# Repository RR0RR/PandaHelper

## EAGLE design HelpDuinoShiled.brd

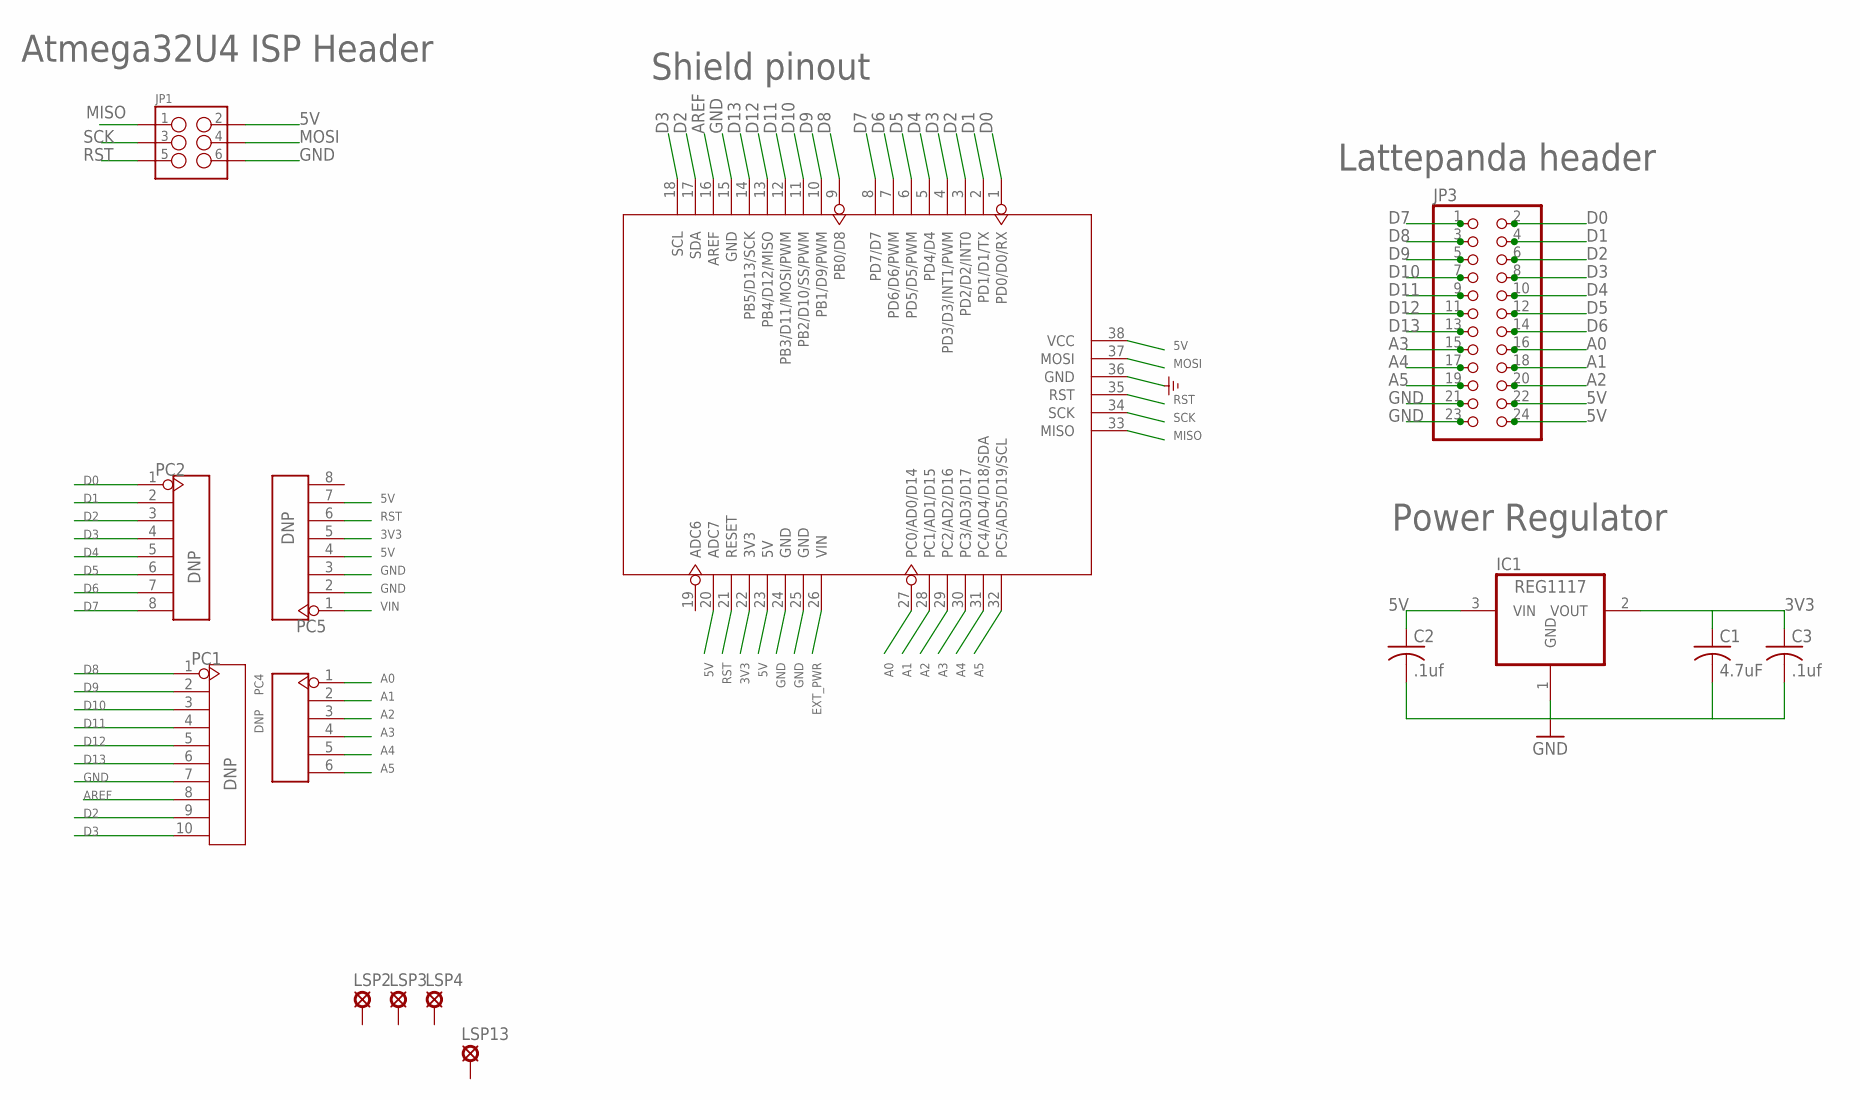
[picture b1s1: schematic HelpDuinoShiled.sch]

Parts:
C1: 4.7uF; C0603K
C2, C3: .1uf; C0603K
IC1: REG1117; SOT223
JP1: M03X2NO_SILK; 2X3-NS
JP3: PINHD-2X12; 2X12
LSP2, LSP3, LSP4, LSP13: SE13
PC1: DNP; 10P-2.54
PC2, PC5: DNP; 8P-2.54
PC4: DNP; 6P-2.54-65/35MIL
U1: ARDUINO-38PWITH/-SILK; ARDUINO-38P-WITH/-SILK-500519002

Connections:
3V3: C1.1, C3.1, IC1.2 (VOUT), PC5.5, U1.22 (3V3)
5V: C2.1, IC1.3 (VIN), JP1.2, JP3.22, JP3.24, PC5.4, PC5.7, U1.20 (ADC7), U1.23 (5V), U1.38 (VCC)
A0: JP3.16, PC4.1, U1.27 (PC0/AD0/D14)
A1: JP3.18, PC4.2, U1.28 (PC1/AD1/D15)
A2: JP3.20, PC4.3, U1.29 (PC2/AD2/D16)
A3: JP3.15, PC4.4, U1.30 (PC3/AD3/D17)
A4: JP3.17, PC4.5, U1.31 (PC4/AD4/D18/SDA)
A5: JP3.19, PC4.6, U1.32 (PC5/AD5/D19/SCL)
AREF: PC1.8, U1.16 (AREF)
D0: JP3.2, PC2.1, U1.1 (PD0/D0/RX)
D1: JP3.4, PC2.2, U1.2 (PD1/D1/TX)
D2: JP3.6, PC1.9, PC2.3, U1.3 (PD2/D2/INT0), U1.17 (SDA)
D3: JP3.8, PC1.10, PC2.4, U1.4 (PD3/D3/INT1/PWM), U1.18 (SCL)
D4: JP3.10, PC2.5, U1.5 (PD4/D4)
D5: JP3.12, PC2.6, U1.6 (PD5/D5/PWM)
D6: JP3.14, PC2.7, U1.7 (PD6/D6/PWM)
D7: JP3.1, PC2.8, U1.8 (PD7/D7)
D8: JP3.3, PC1.1, U1.9 (PB0/D8)
D9: JP3.5, PC1.2, U1.10 (PB1/D9/PWM)
D10: JP3.7, PC1.3, U1.11 (PB2/D10/SS/PWM)
D11: JP3.9, PC1.4, U1.12 (PB3/D11/MOSI/PWM)
D12: JP3.11, PC1.5, U1.13 (PB4/D12/MISO)
D13: JP3.13, PC1.6, U1.14 (PB5/D13/SCK)
EXT_PWR: U1.26 (VIN)
GND: C1.2, C2.2, C3.2, IC1.1 (GND), JP1.6, JP3.21, JP3.23, PC1.7, PC5.2, PC5.3, U1.15 (GND), U1.24 (GND), U1.25 (GND), U1.36 (GND)
MISO: JP1.1, U1.33 (MISO)
MOSI: JP1.4, U1.37 (MOSI)
RST: JP1.5, PC5.6, U1.21 (RESET), U1.35 (RST)
SCK: JP1.3, U1.34 (SCK)
VIN: PC5.1

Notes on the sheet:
Atmega32U4 ISP Header
Lattepanda header
Shield pinout
Power Regulator

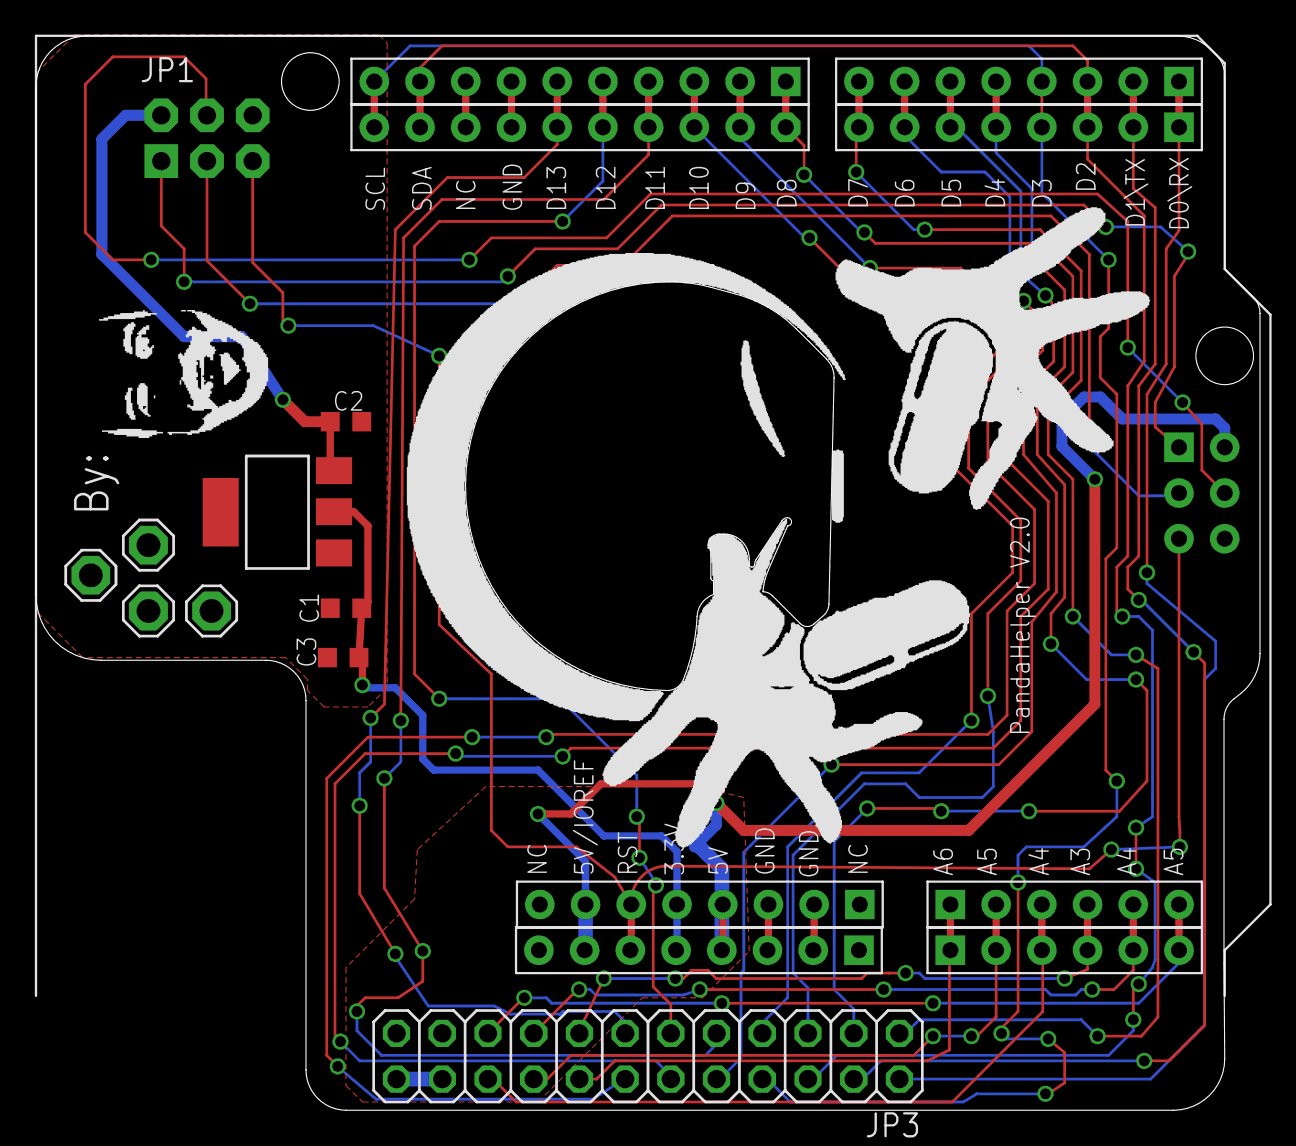
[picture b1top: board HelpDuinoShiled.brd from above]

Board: 2 copper layers, 68.0 x 59.7 mm, 17 parts (0 on the bottom side), 28 nets.

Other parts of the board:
U$1: OBSIDISLOGO
U$2: FACELOGO

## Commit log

2016-11-09 initital commit
2016-11-09 adding traces
2016-11-10 added 3.3v
2016-11-11 Finalizing V2 and Ordering
2016-11-17 Adding screenshots

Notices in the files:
parts and their libraries:
SparkFun-Connectors: Licensing: Creative Commons ShareAlike 4.0 International - https://creativecommons.org/licenses/by-sa/4.0
